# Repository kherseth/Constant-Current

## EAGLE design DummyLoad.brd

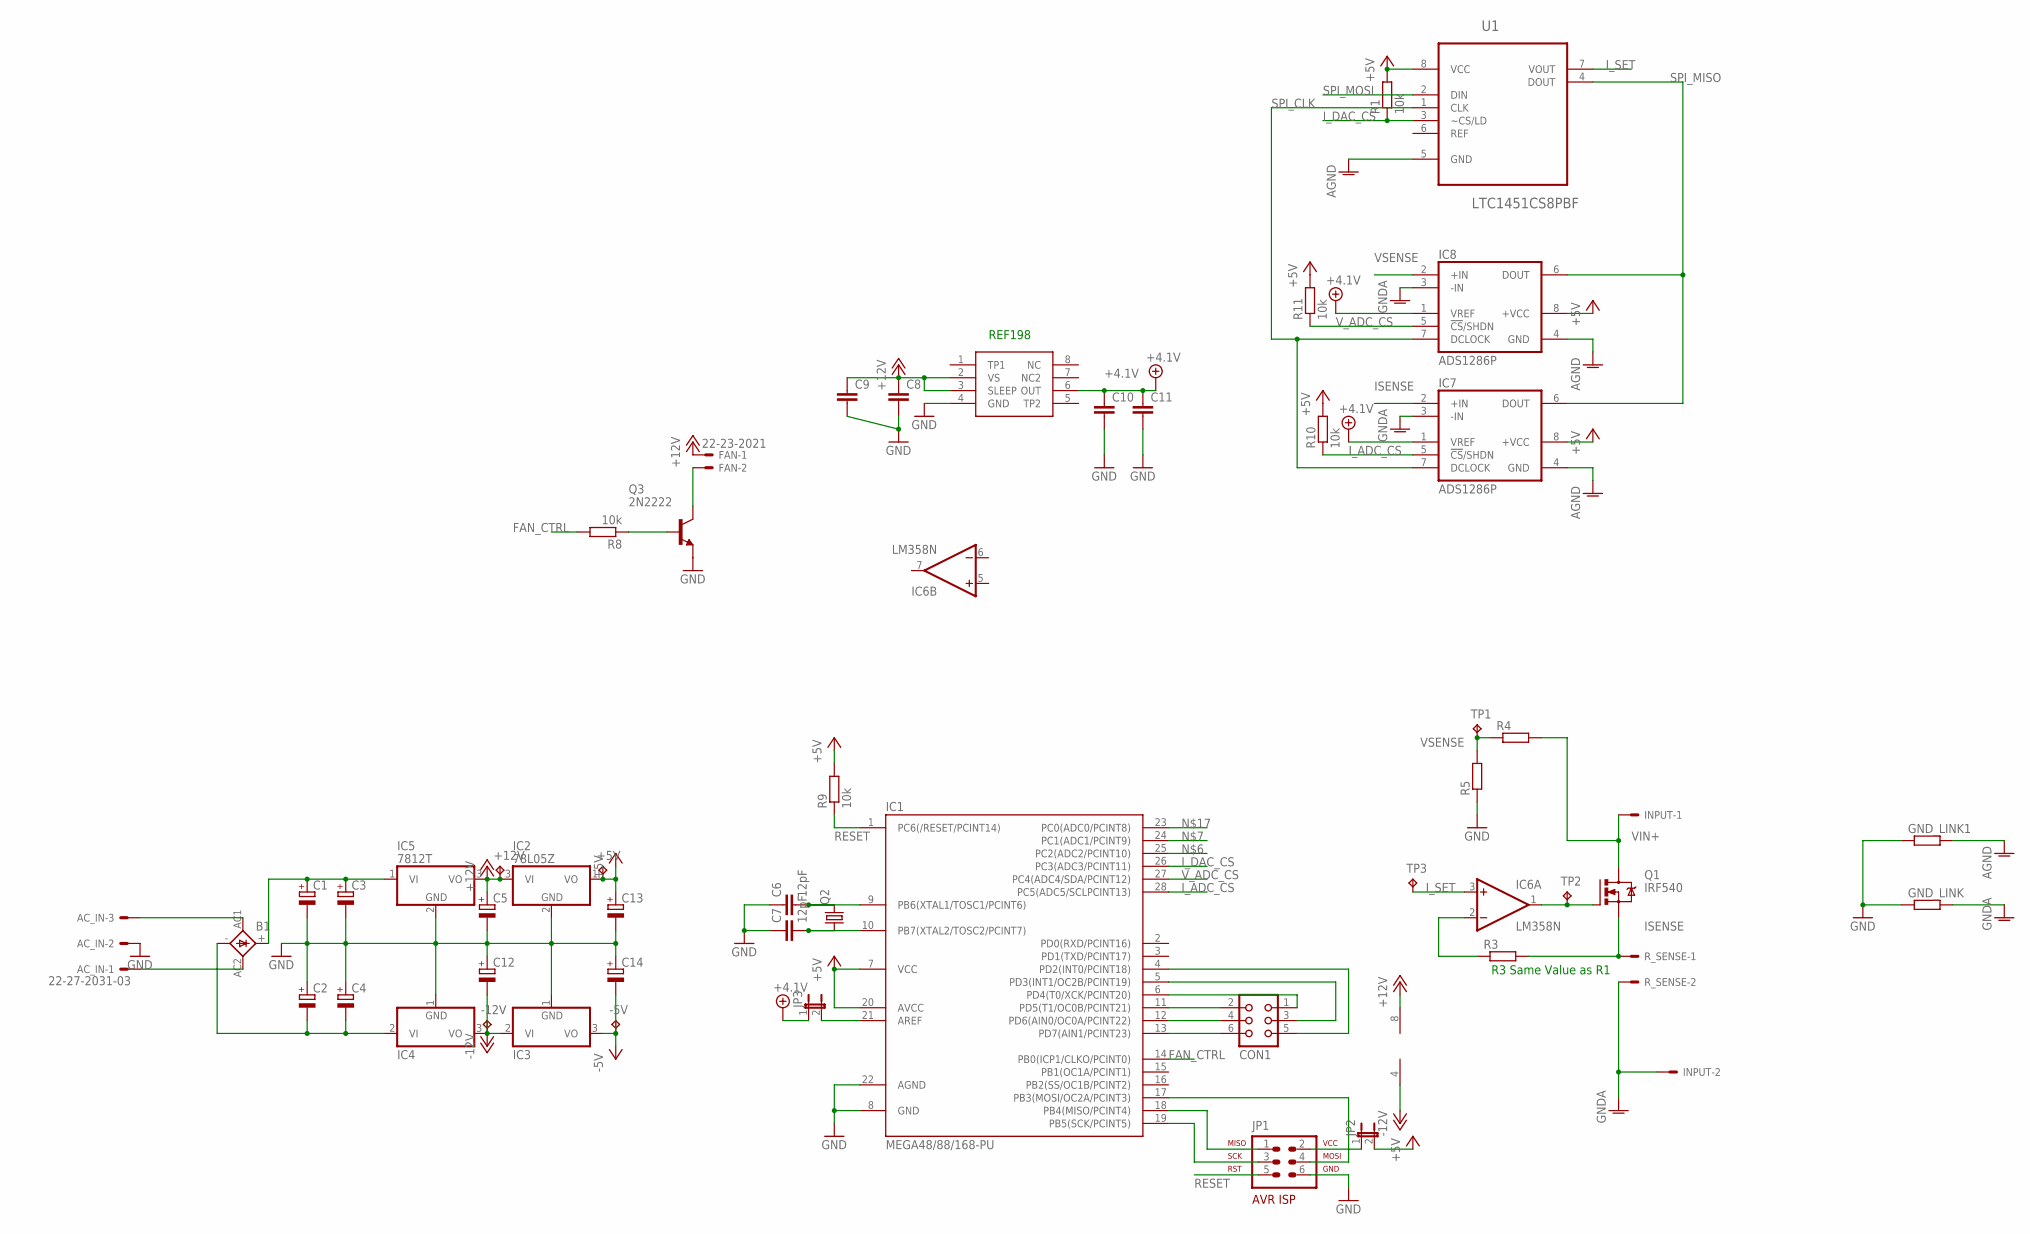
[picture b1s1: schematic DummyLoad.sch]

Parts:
+5V, +12V: TPB2,54; B2,54
-5V, -12V: TPB2,54; B2,54
AC_IN: 22-27-2031-03; 6410-03
B1: 2KBB-R
C1, C2, C3, C4: CPOL-EUE5-8.5; E5-8,5
C5, C12, C13, C14: CPOL-EUE2,5-6E; E2,5-6E
C6, C7: 12pF; C1206K
C8, C9, C10, C11: C-EUC1206K; C1206K
CON1: CON06
FAN: 22-23-2021
GND_LINK, GND_LINK1: R-EU_0204/2V; 0204V
IC1: MEGA48/88/168-PU; DIL28-3
IC2: 78L05Z; TO92
IC3: 79L05Z; TO92
IC4: 7912T; TO220H
IC5: 7812T; TO220H
IC6: LM358N; DIL08
IC7, IC8: ADS1286P; DIL08
INPUT: KK-156-2
JP1: AVR-ISP-6VERT; AVR-ISP-6
JP2, JP3: JP1E; JP1
Q1: IRF540; TO220BV
Q2: CRYSTALHC18U-V; HC18U-V
Q3: 2N2222; TO18
R1, R9, R10, R11: 10k; M1206
R3, R4, R5: R-EU_M1206; M1206
R8: 10k; 0204/7
R_SENSE: KK-156-2
TP1, TP2, TP3: TPB2,54; B2,54
U1: LTC1451CS8PBF; SOIC127P600X175-8N
U$1: REF195; DIL08

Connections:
+4.1V: C10.1, C11.1, IC7.1 (VREF), IC8.1 (VREF), JP3.1, U$1.6 (OUT)
+5V: +5V.TP, C13.+, IC1.7 (VCC), IC1.20 (AVCC), IC2.1 (VO), IC7.8 (+VCC), IC8.8 (+VCC), JP2.2, R1.2, R9.2, R10.2, R11.2, U1.8 (VCC)
+12V: +12V.TP, C5.+, C8.1, C9.1, FAN.1, IC2.3 (VI), IC5.3 (VO), IC6.8 (V+), U$1.2 (VS), U$1.3 (SLEEP)
-5V: -5V.TP, C14.-, IC3.3 (VO)
-12V: -12V.TP, C12.-, IC3.2 (VI), IC4.3 (VO), IC6.4 (V-)
AGND: GND_LINK1.2, IC7.4 (GND), IC8.4 (GND), U1.5 (GND)
FAN_CTRL: IC1.14 (PB0(ICP1/CLKO/PCINT0)), R8.2
GND: AC_IN.2, C1.-, C2.+, C3.-, C4.+, C5.-, C6.1, C7.1, C8.2, C9.2, C10.2, C11.2, C12.+, C13.-, C14.+, GND_LINK.1, GND_LINK1.1, IC1.8 (GND), IC1.22 (AGND), IC2.2 (GND), IC3.1 (GND), IC4.1 (GND), IC5.2 (GND), JP1.6, Q3.1 (E), R5.1, U$1.4 (GND)
GNDA: GND_LINK.2, IC7.3 (-IN), IC8.3 (-IN), INPUT.2, R_SENSE.2
ISENSE: IC7.2 (+IN), Q1.S, R3.2, R_SENSE.1
I_ADC_CS: IC1.28 (PC5(ADC5/SCLPCINT13)), IC7.5 (!CS!/SHDN), R10.1
I_DAC_CS: IC1.26 (PC3(ADC3/PCINT11)), R1.1, U1.3 (~CS/LD)
I_SET: IC6.3 (+IN), TP3.TP, U1.7 (VOUT)
unnamed: AC_IN.3, B1.AC1
unnamed: AC_IN.1, B1.AC2
unnamed: B1.+, C1.+, C3.+, IC5.1 (VI)
unnamed: IC6.1 (OUT), Q1.G, TP2.TP
unnamed: IC1.21 (AREF), JP3.2
unnamed: B1.-, C2.-, C4.-, IC4.2 (VI)
unnamed: CON1.2, IC1.11 (PD5(T1/OC0B/PCINT21))
unnamed: CON1.4, IC1.12 (PD6(AIN0/OC0A/PCINT22))
unnamed: CON1.6, IC1.13 (PD7(AIN1/PCINT23))
unnamed: CON1.1, IC1.6 (PD4(T0/XCK/PCINT20))
unnamed: CON1.3, IC1.5 (PD3(INT1/OC2B/PCINT19))
unnamed: C6.2, IC1.9 (PB6(XTAL1/TOSC1/PCINT6)), Q2.2
unnamed: C7.2, IC1.10 (PB7(XTAL2/TOSC2/PCINT7)), Q2.1
unnamed: CON1.5, IC1.4 (PD2(INT0/PCINT18))
unnamed: FAN.2, Q3.3 (C)
unnamed: Q3.2 (B), R8.1
unnamed: JP1.2, JP2.1
RESET: IC1.1 (PC6(/RESET/PCINT14)), JP1.5, R9.1
R_SENSE+: IC6.2 (-IN), R3.1
SPI_CLK: IC1.19 (PB5(SCK/PCINT5)), IC7.7 (DCLOCK), IC8.7 (DCLOCK), JP1.3, U1.1 (CLK)
SPI_MISO: IC1.18 (PB4(MISO/PCINT4)), IC7.6 (DOUT), IC8.6 (DOUT), JP1.1, U1.4 (DOUT)
SPI_MOSI: IC1.17 (PB3(MOSI/OC2A/PCINT3)), JP1.4, U1.2 (DIN)
VIN+: INPUT.1, Q1.D, R4.2
VSENSE: IC8.2 (+IN), R4.1, R5.2, TP1.TP
V_ADC_CS: IC1.27 (PC4(ADC4/SDA/PCINT12)), IC8.5 (!CS!/SHDN), R11.1

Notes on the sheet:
R3 Same Value as R1
REF198

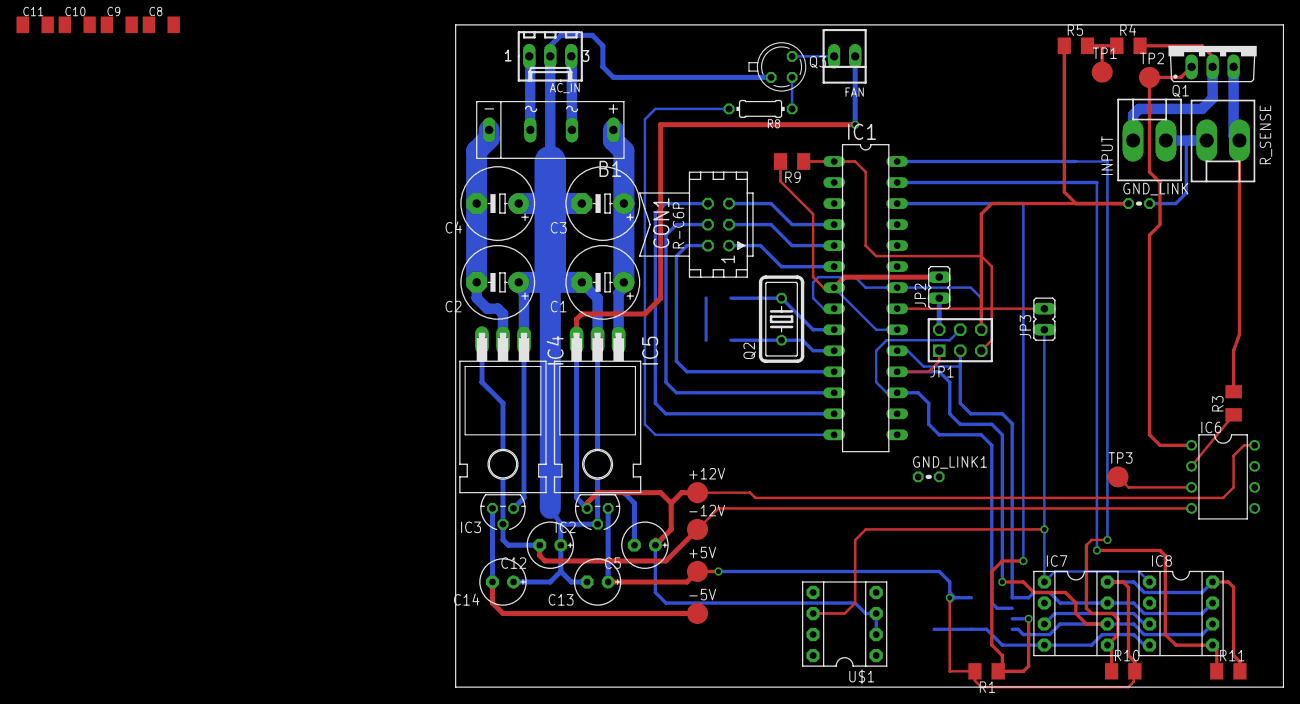
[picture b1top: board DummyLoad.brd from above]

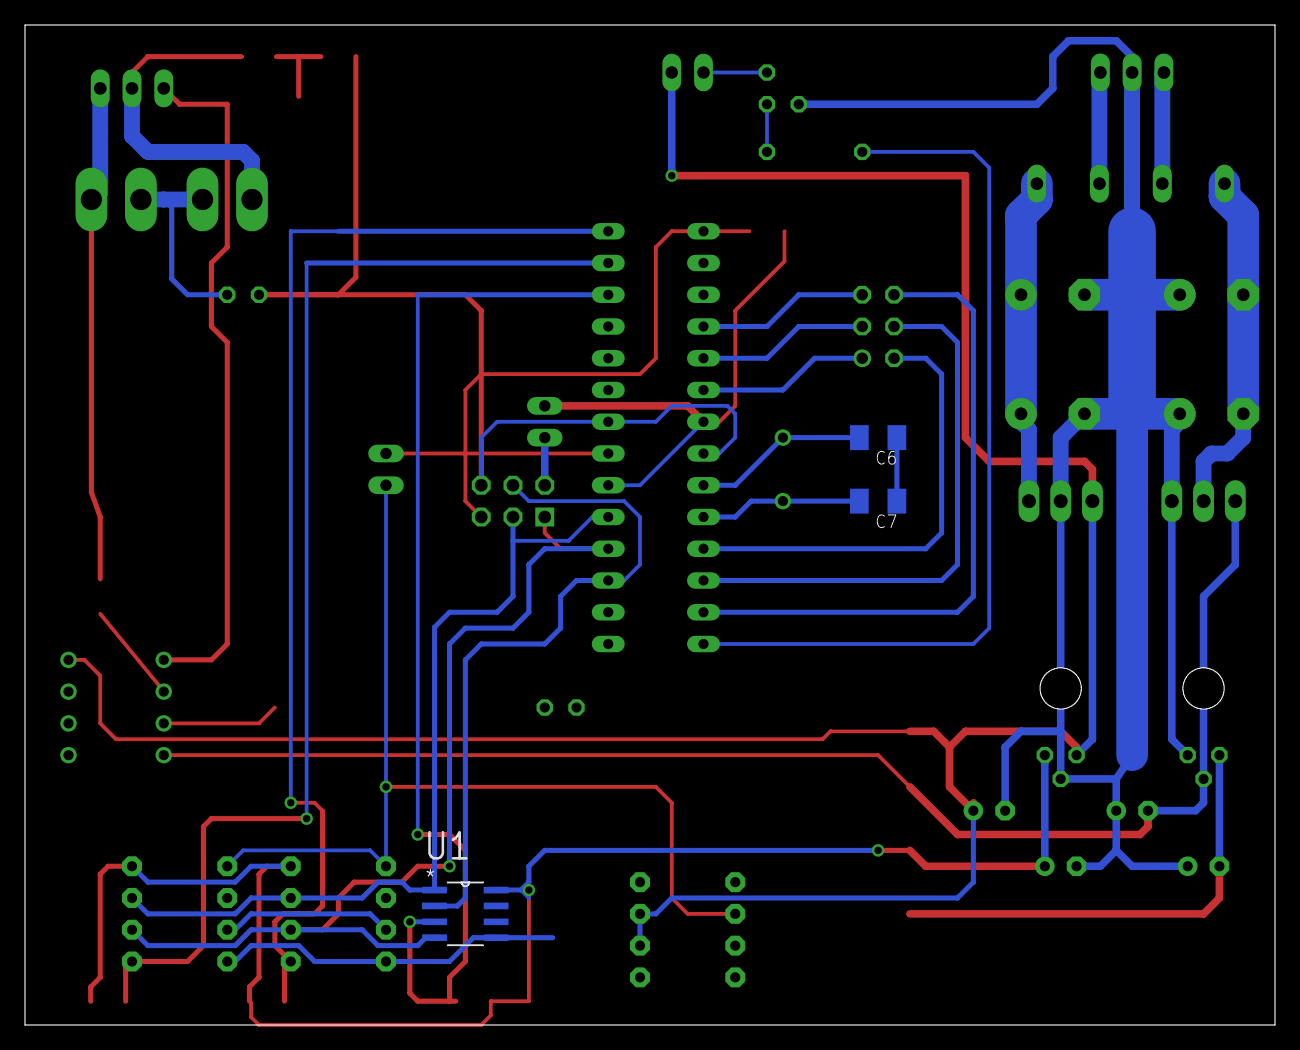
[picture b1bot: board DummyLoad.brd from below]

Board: 2 copper layers, 100.0 x 80.0 mm, 53 parts (3 on the bottom side), 38 nets.

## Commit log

2015-05-28 :lollipop: Added .gitattributes & .gitignore files
2015-05-28 Dummy Load
